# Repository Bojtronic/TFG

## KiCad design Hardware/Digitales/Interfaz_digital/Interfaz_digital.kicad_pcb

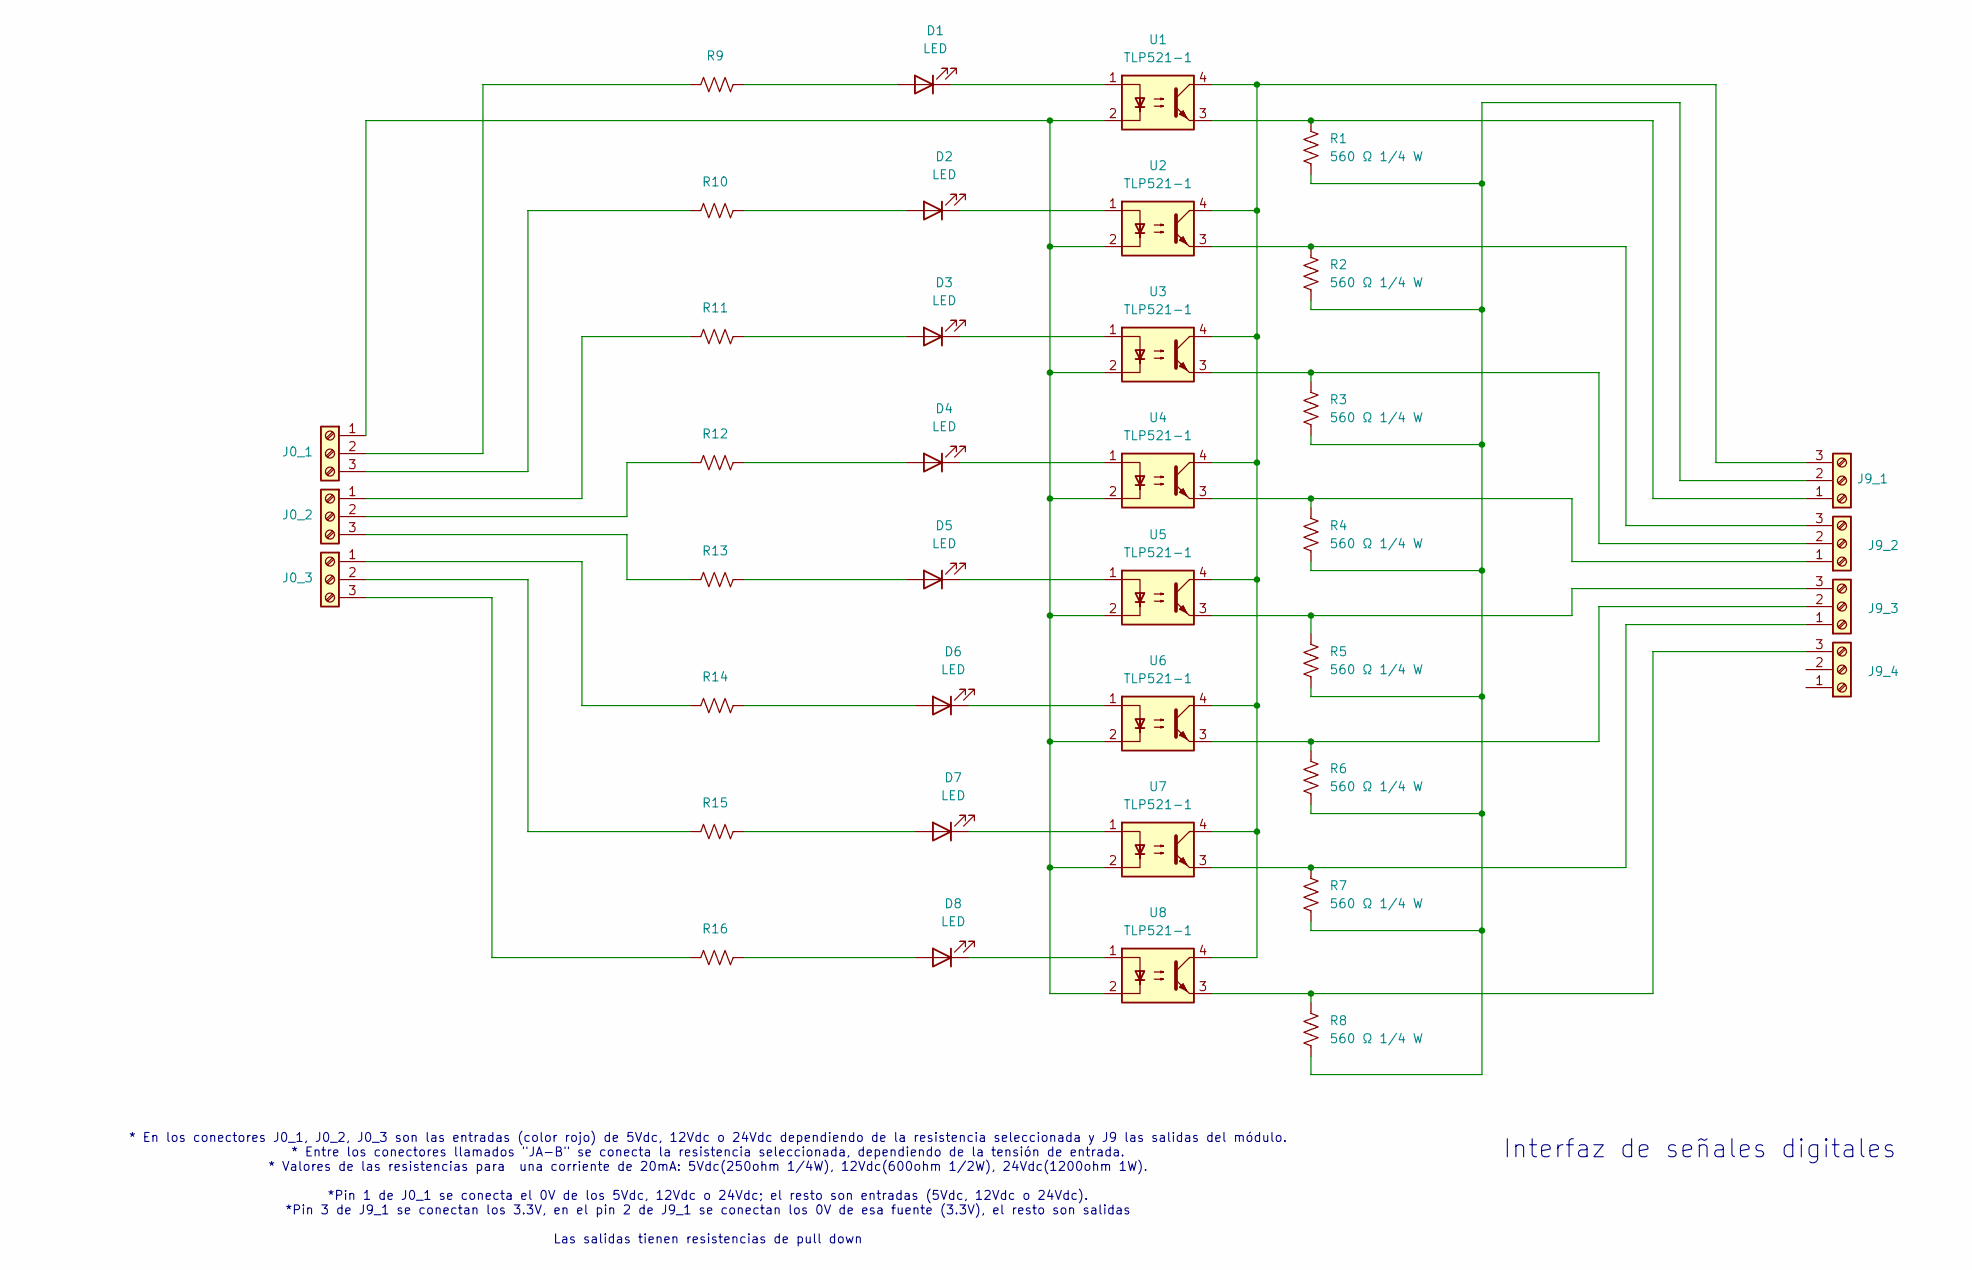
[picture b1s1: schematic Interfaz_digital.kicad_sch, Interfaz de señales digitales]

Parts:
D1, D2, D3, D4, D5, D6, D7, D8: LED; LED_D4.0mm
J0_1, J0_2, J0_3, J9_1, J9_2, J9_3, J9_4: Screw_Terminal_01x03; TerminalBlock_Phoenix_PT-1,5-3-3.5-H_1x03_P3.50mm_Horizontal
R1, R2, R3, R4, R5, R6, R7, R8: 560 Ω 1/4 W; R_Axial_DIN0207_L6.3mm_D2.5mm_P10.16mm_Horizontal
R9, R10, R11, R12, R13, R14, R15, R16: R_US; R_Axial_DIN0207_L6.3mm_D2.5mm_P7.62mm_Horizontal
U1, U2, U3, U4, U5, U6, U7, U8: TLP521-1; DIP-4_W7.62mm

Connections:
unnamed: D1.2 (A), R9.2
unnamed: D1.1 (K), U1.1
unnamed: D2.2 (A), R10.2
unnamed: D2.1 (K), U2.1
unnamed: D3.2 (A), R11.2
unnamed: D3.1 (K), U3.1
unnamed: D4.2 (A), R12.2
unnamed: D4.1 (K), U4.1
unnamed: D5.2 (A), R13.2
unnamed: D5.1 (K), U5.1
unnamed: D6.2 (A), R14.2
unnamed: D6.1 (K), U6.1
unnamed: D7.2 (A), R15.2
unnamed: D7.1 (K), U7.1
unnamed: D8.2 (A), R16.2
unnamed: D8.1 (K), U8.1
unnamed: J0_1.1, U1.2, U2.2, U3.2, U4.2, U5.2, U6.2, U7.2, U8.2
unnamed: J0_1.2, R9.1
unnamed: J0_1.3, R10.1
unnamed: J0_2.1, R11.1
unnamed: J0_2.2, R12.1
unnamed: J0_2.3, R13.1
unnamed: J0_3.1, R14.1
unnamed: J0_3.2, R15.1
unnamed: J0_3.3, R16.1
unnamed: J9_1.1, R1.1, U1.3
unnamed: J9_1.2, R1.2, R2.2, R3.2, R4.2, R5.2, R6.2, R7.2, R8.2
unnamed: J9_1.3, U1.4, U2.4, U3.4, U4.4, U5.4, U6.4, U7.4, U8.4
unnamed: J9_2.1, R4.1, U4.3
unnamed: J9_2.2, R3.1, U3.3
unnamed: J9_2.3, R2.1, U2.3
unnamed: J9_3.1, R7.1, U7.3
unnamed: J9_3.2, R6.1, U6.3
unnamed: J9_3.3, R5.1, U5.3
unnamed: J9_4.3, R8.1, U8.3

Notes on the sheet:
Interfaz de señales digitales
* En los conectores J0_1, J0_2, J0_3 son las entradas (color rojo) de 5Vdc, 12Vdc o 24Vdc dependiendo de la resistencia seleccionada y J9 las salidas del módulo. * Entre los conectores llamados "JA-B" se conecta la resistencia seleccionada, dependiendo de la tensión de entrada. * Valores de las res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

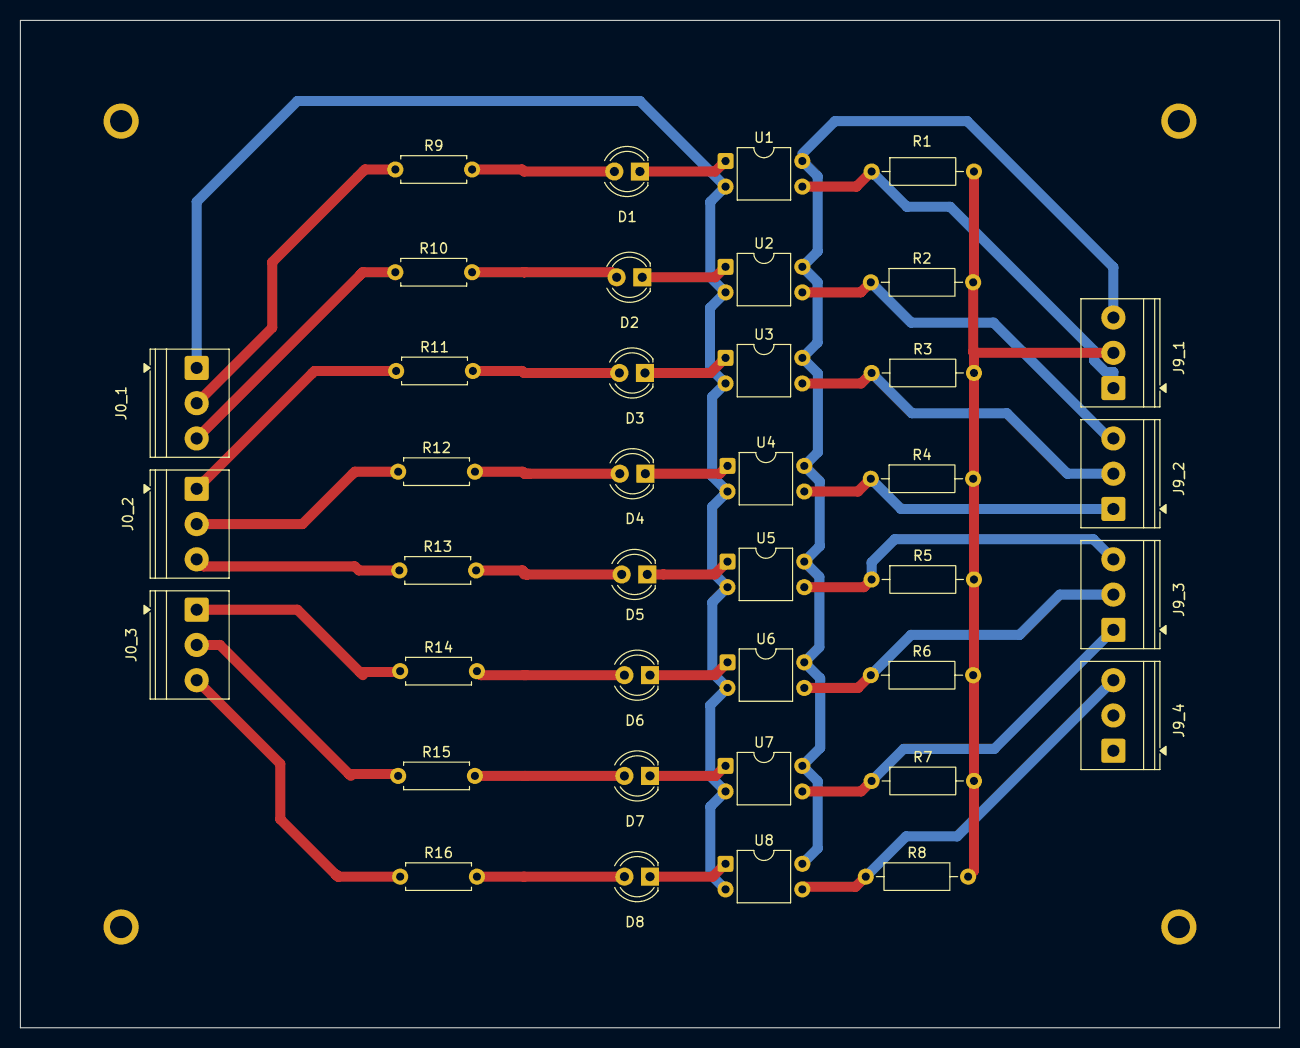
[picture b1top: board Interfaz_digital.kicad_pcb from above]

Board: 2 copper layers, 125.0 x 100.0 mm, 43 parts (0 on the bottom side), 35 nets.

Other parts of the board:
H1, H2, H3, H4: MountingHole_2.2mm_M2_ISO7380_Pad

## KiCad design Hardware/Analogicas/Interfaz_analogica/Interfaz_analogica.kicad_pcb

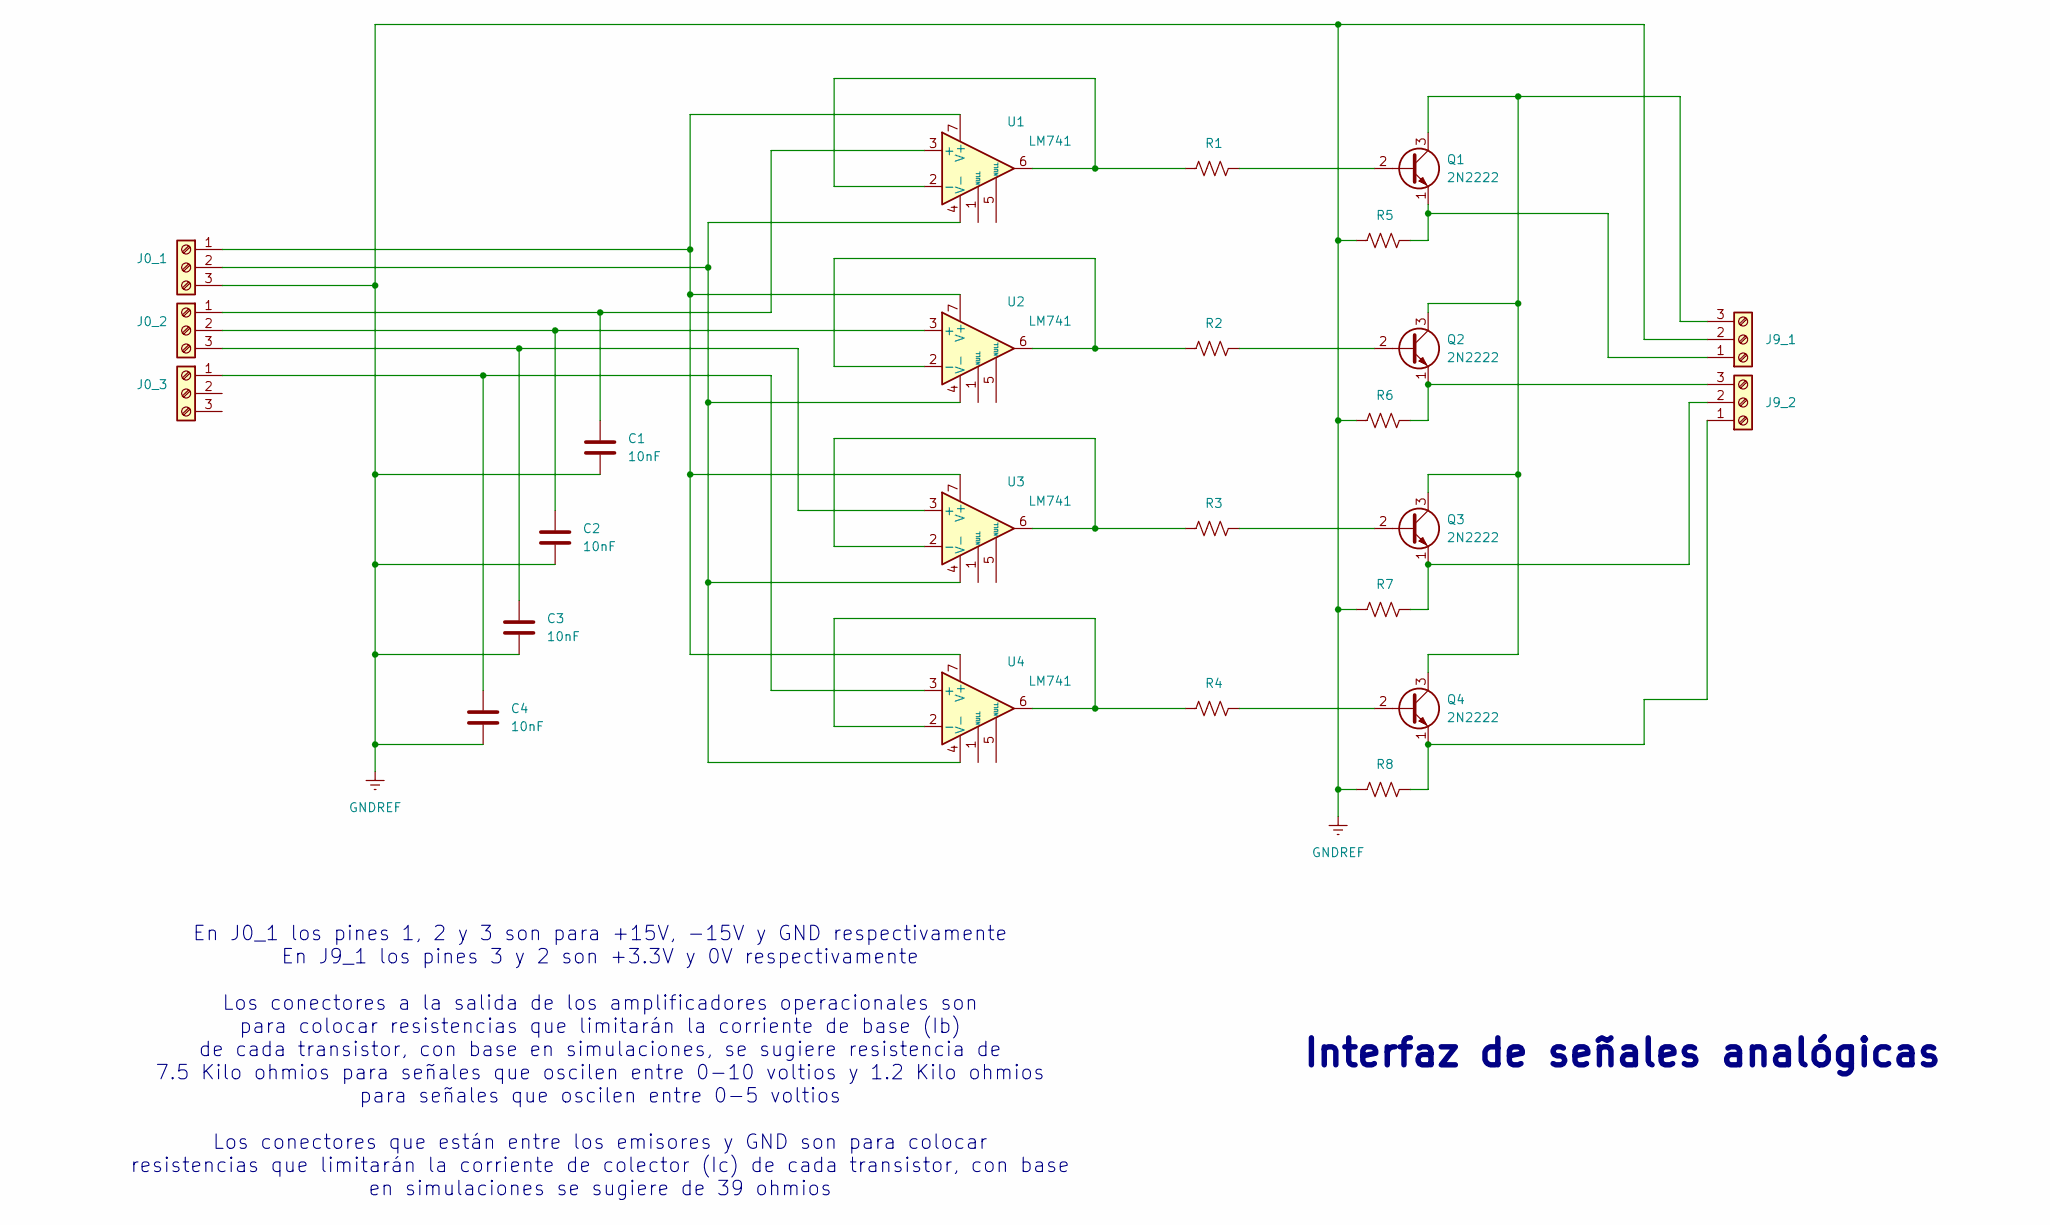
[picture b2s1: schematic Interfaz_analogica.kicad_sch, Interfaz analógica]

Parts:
C1, C2, C3, C4: 10nF; C_Disc_D4.3mm_W1.9mm_P5.00mm
J0_1, J0_2, J0_3, J9_1, J9_2: Screw_Terminal_01x03; TerminalBlock_Phoenix_PT-1,5-3-3.5-H_1x03_P3.50mm_Horizontal
Q1, Q2, Q3, Q4: 2N2222; TO-39-3
R1, R2, R3, R4, R5, R6, R7, R8: R_US; R_Axial_DIN0207_L6.3mm_D2.5mm_P7.62mm_Horizontal
U1, U2, U3, U4: LM741; LM741_TH

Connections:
GNDREF: C1.2, C2.2, C3.2, C4.2, J0_1.3, J9_1.2, R5.1, R6.1, R7.1, R8.1
unnamed: J0_1.1, U1.7 (V+), U2.7 (V+), U3.7 (V+), U4.7 (V+)
unnamed: J0_1.2, U1.4 (V-), U2.4 (V-), U3.4 (V-), U4.4 (V-)
unnamed: C1.1, J0_2.1, U1.3 (+)
unnamed: C2.1, J0_2.2, U2.3 (+)
unnamed: C3.1, J0_2.3, U3.3 (+)
unnamed: C4.1, J0_3.1, U4.3 (+)
unnamed: J9_1.1, Q1.1 (E), R5.2
unnamed: J9_1.3, Q1.3 (C), Q2.3 (C), Q3.3 (C), Q4.3 (C)
unnamed: J9_2.1, Q4.1 (E), R8.2
unnamed: J9_2.2, Q3.1 (E), R7.2
unnamed: J9_2.3, Q2.1 (E), R6.2
unnamed: Q1.2 (B), R1.2
unnamed: Q2.2 (B), R2.2
unnamed: Q3.2 (B), R3.2
unnamed: Q4.2 (B), R4.2
unnamed: R1.1, U1.2 (-), U1.6
unnamed: R2.1, U2.2 (-), U2.6
unnamed: R3.1, U3.2 (-), U3.6
unnamed: R4.1, U4.2 (-), U4.6

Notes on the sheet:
En J0_1 los pines 1, 2 y 3 son para +15V, -15V y GND respectivamente En J9_1 los pines 3 y 2 son +3.3V y 0V respectivamente Los conectores a la salida de los amplificadores operacionales son para colocar resistencias que limitarán la corriente de base (Ib) de cada transistor, con base en simulacion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
Interfaz de señales analógicas

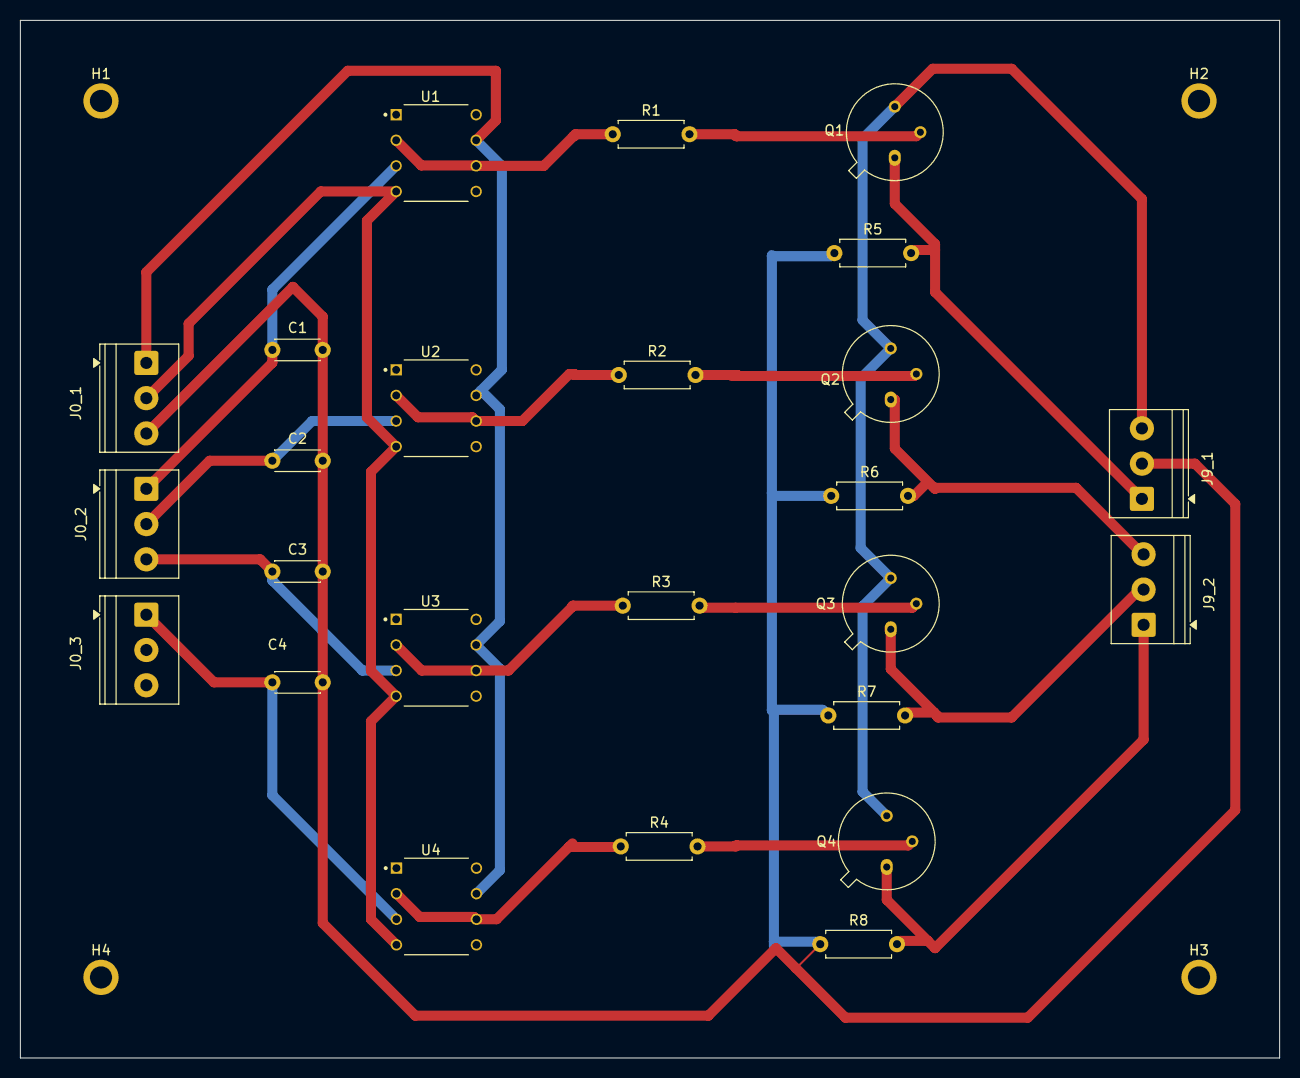
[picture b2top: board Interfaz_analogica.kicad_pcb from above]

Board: 2 copper layers, 125.0 x 103.0 mm, 29 parts (0 on the bottom side), 20 nets.

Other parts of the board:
H1, H2, H3, H4: MountingHole_2.2mm_M2_ISO7380_Pad
